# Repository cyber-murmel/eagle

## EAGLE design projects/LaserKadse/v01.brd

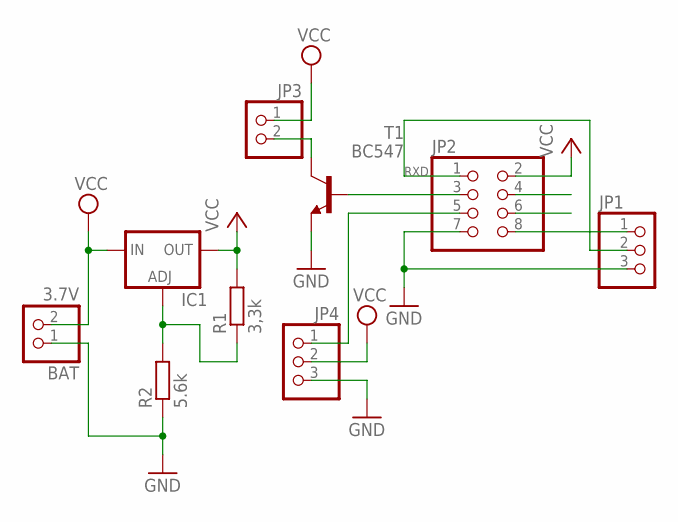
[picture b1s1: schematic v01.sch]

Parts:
BAT: 3.7V; 1X02/90
IC1: LM317TL; 317TL
JP1: PINHD-1X3/90; 1X03/90
JP2: PINHD-2X4; 2X04
JP3: PINHD-1X2; 1X02
JP4: PINHD-1X3; 1X03
R1: 3,3k; 0207/10
R2: 5.6k; 0207/10
T1: BC547; TO92

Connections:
BAT: BAT.2, IC1.3 (IN), JP3.1, JP4.2
CHPD: JP2.6
GND: BAT.1, JP1.3, JP2.7, JP4.3, R2.1, T1.1 (E)
GPIO0: JP2.3, T1.2 (B)
GPIO2: JP2.5, JP4.1
unnamed: IC1.1 (ADJ), R1.1, R2.2
unnamed: JP3.2, T1.3 (C)
unnamed: JP1.1, JP2.8
RST: JP2.4
RXD: JP1.2, JP2.1
VCC: IC1.2 (OUT), JP2.2, R1.2

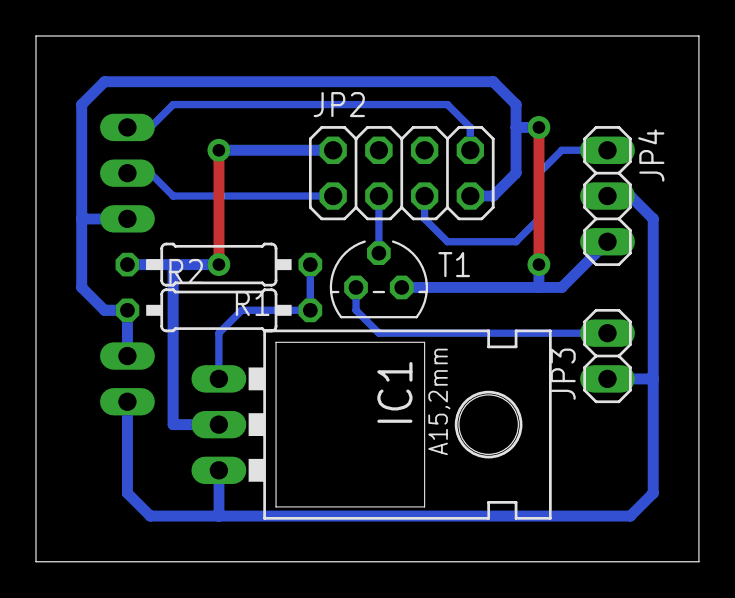
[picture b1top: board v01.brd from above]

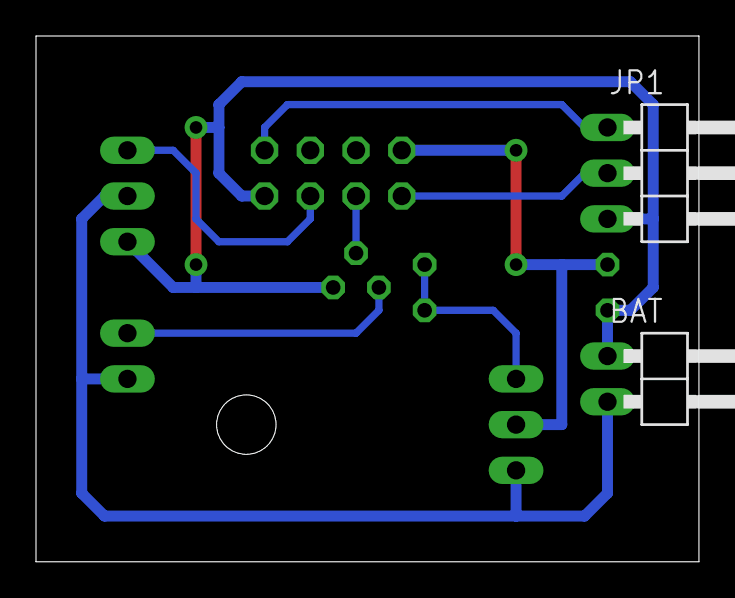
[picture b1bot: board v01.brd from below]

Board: 2 copper layers, 36.8 x 29.2 mm, 9 parts (2 on the bottom side), 9 nets.

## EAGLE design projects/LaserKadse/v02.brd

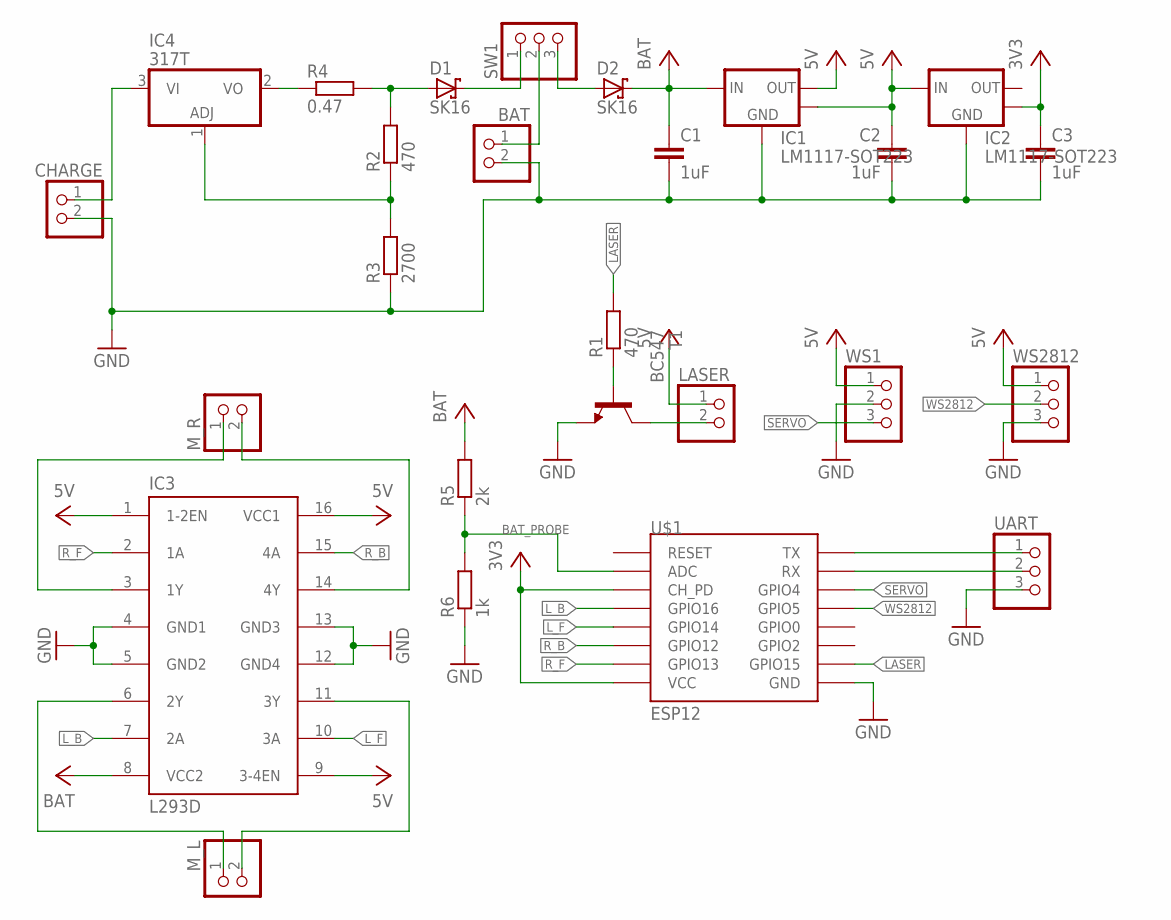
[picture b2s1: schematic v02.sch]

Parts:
BAT: PINHD-1X2; 1X02
C1, C2, C3: 1uF; C0805
CHARGE: PINHD-1X2; 1X02
D1, D2: SK16; SMB
IC1, IC2: LM1117-SOT223; SOT-223-3
IC3: L293D; DIL16
IC4: 317T; TO220H
LASER: PINHD-1X2; 1X02
M_L: PINHD-1X2; 1X02
M_R: PINHD-1X2; 1X02
R1, R2: 470; R0805
R3: 2700; R0805
R4: 0.47; MINI_MELF-0207W
R5: 2k; R0805
R6: 1k; R0805
SW1: PINHD-1X3; 1X03
T1: BC547; TO92
U$1: ESP12
UART: PINHD-1X3; 1X03
WS1, WS2812: PINHD-1X3; 1X03

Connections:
3V3: C3.1, IC2.4 (HEATSINK), U$1.CH_PD, U$1.VCC
5V: C2.1, IC1.4 (HEATSINK), IC2.3 (VIN), LASER.1, WS1.1, WS2812.1
5V_2: IC1.2 (VOUT), IC3.1 (1-2EN), IC3.9 (3-4EN), IC3.16 (VCC1)
BAT: C1.1, D2.C, IC1.3 (VIN), IC3.8 (VCC2), R5.2
BAT_PROBE: R5.1, R6.2, U$1.ADC
GND: BAT.2, C1.2, C2.2, C3.2, CHARGE.2, IC1.1 (GND), IC2.1 (GND), IC3.4 (GND1), IC3.5 (GND2), IC3.12 (GND4), IC3.13 (GND3), R3.1, R6.1, T1.1 (E), U$1.GND, UART.3, WS1.2, WS2812.3
LASER: R1.2, U$1.GPIO15
L_B: IC3.7 (2A), U$1.GPIO16
L_F: IC3.10 (3A), U$1.GPIO14
unnamed: BAT.1, SW1.2
unnamed: R1.1, T1.2 (B)
unnamed: CHARGE.1, IC4.3 (VI)
unnamed: D1.C, SW1.1
unnamed: IC3.3 (1Y), M_R.1
unnamed: IC3.14 (4Y), M_R.2
unnamed: IC3.6 (2Y), M_L.1
unnamed: IC3.11 (3Y), M_L.2
unnamed: U$1.TX, UART.1
unnamed: U$1.RX, UART.2
unnamed: LASER.2, T1.3 (C)
unnamed: D1.A, R2.2, R4.2
unnamed: IC4.1 (ADJ), R2.1, R3.2
unnamed: IC4.2 (VO), R4.1
unnamed: D2.A, SW1.3
R_B: IC3.15 (4A), U$1.GPIO12
R_F: IC3.2 (1A), U$1.GPIO13
SERVO: U$1.GPIO4, WS1.3
WS2812: U$1.GPIO5, WS2812.2

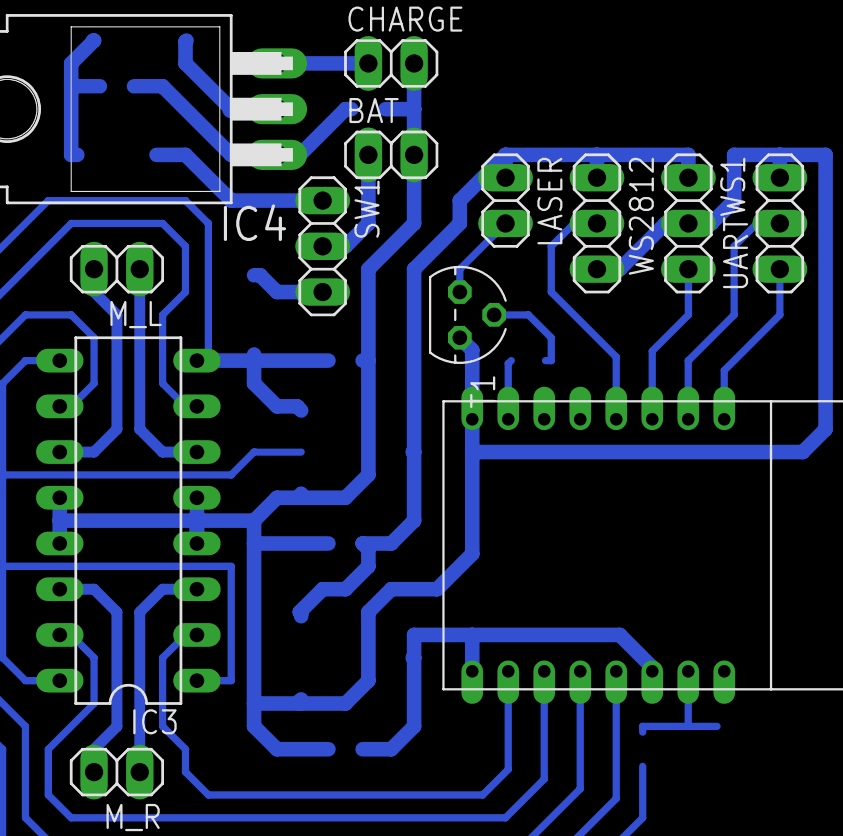
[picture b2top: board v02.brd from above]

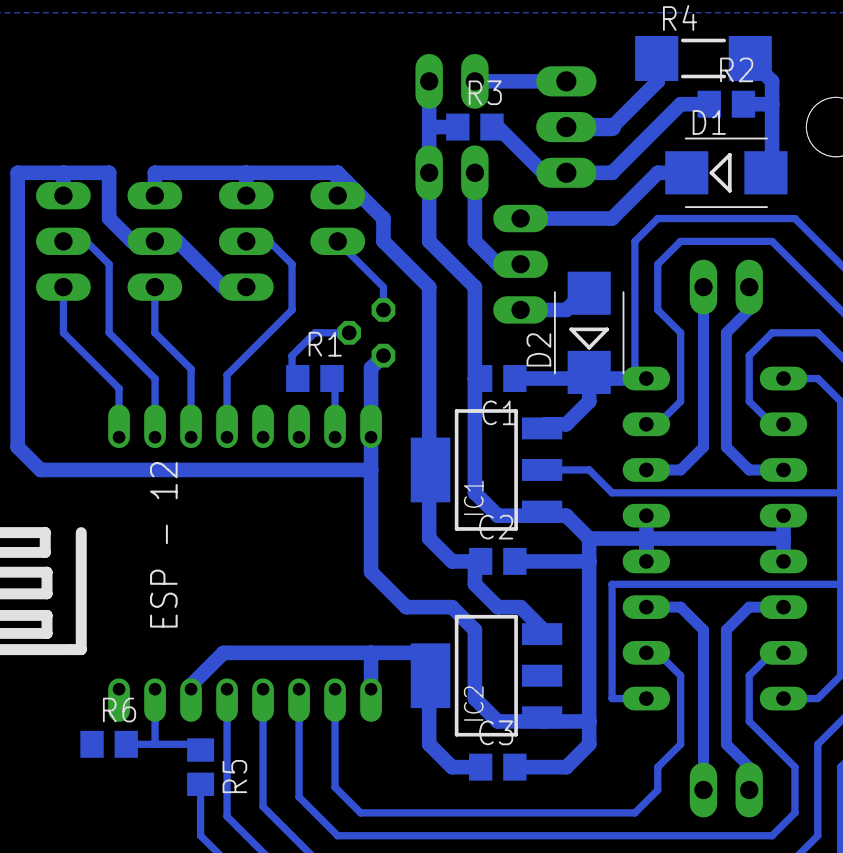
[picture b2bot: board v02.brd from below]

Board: 2 copper layers, 26 parts (14 on the bottom side), 28 nets.

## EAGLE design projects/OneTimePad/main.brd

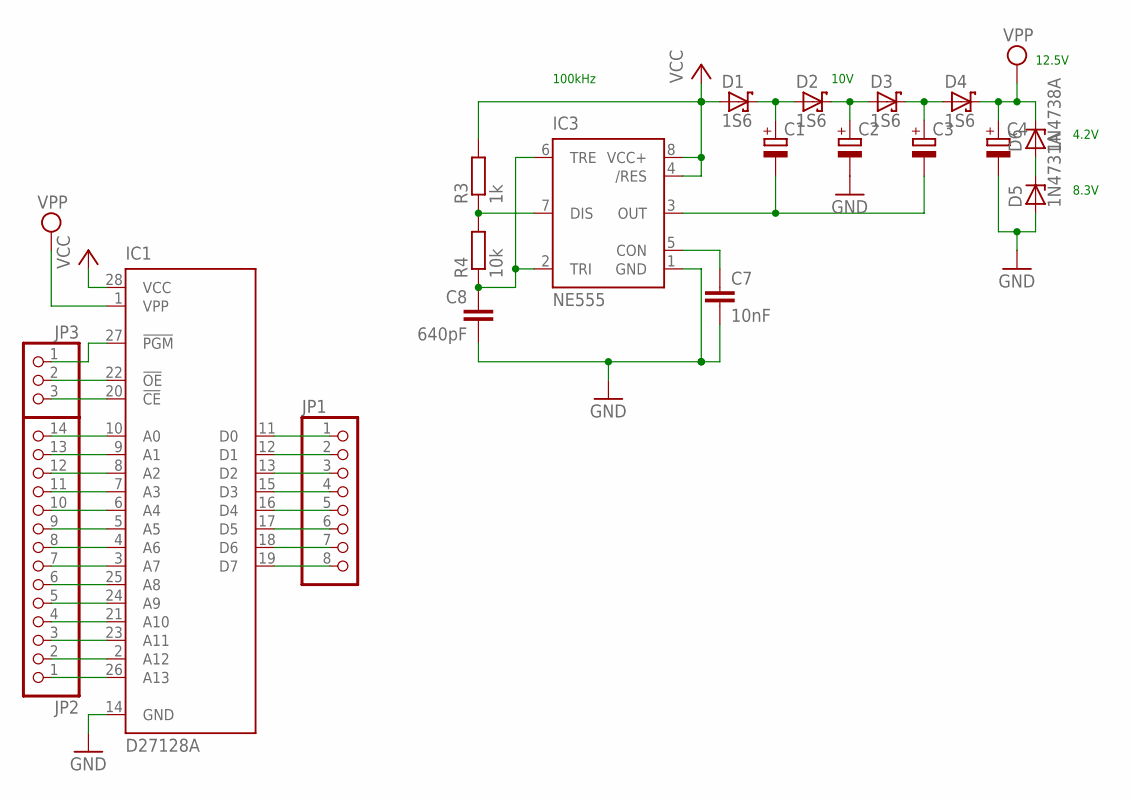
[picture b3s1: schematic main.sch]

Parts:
C1, C2, C3, C4: CPOL-EUB45181A; B45181A
C7: 10nF; C025-025X050
C8: 640pF; C025-025X050
D1, D2, D3, D4: 1S6; DO41-7.6
D5: 1N4731A; DO41Z10
D6: 1N4738A; DO41Z10
IC1: D27128A; DIL28-6
IC3: NE555; DIL-08
JP1: PINHD-1X8; 1X08
JP2: PINHD-1X14; 1X14
JP3: PINHD-1X3; 1X03
R3: 1k; 0204/7
R4: 10k; 0204/7

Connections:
GND: C2.-, C4.-, C7.2, C8.2, D5.A, IC1.14 (GND), IC3.1 (GND)
unnamed: IC1.11 (D0), JP1.1
unnamed: IC1.12 (D1), JP1.2
unnamed: IC1.13 (D2), JP1.3
unnamed: IC1.15 (D3), JP1.4
unnamed: IC1.16 (D4), JP1.5
unnamed: IC1.17 (D5), JP1.6
unnamed: IC1.18 (D6), JP1.7
unnamed: IC1.19 (D7), JP1.8
unnamed: IC1.10 (A0), JP2.14
unnamed: IC1.9 (A1), JP2.13
unnamed: IC1.8 (A2), JP2.12
unnamed: IC1.7 (A3), JP2.11
unnamed: IC1.6 (A4), JP2.10
unnamed: IC1.5 (A5), JP2.9
unnamed: IC1.4 (A6), JP2.8
unnamed: IC1.3 (A7), JP2.7
unnamed: IC1.25 (A8), JP2.6
unnamed: IC1.24 (A9), JP2.5
unnamed: IC1.21 (A10), JP2.4
unnamed: IC1.23 (A11), JP2.3
unnamed: IC1.2 (A12), JP2.2
unnamed: IC1.26 (A13), JP2.1
unnamed: C1.-, C3.-, IC3.3 (OUT)
unnamed: C3.+, D3.C, D4.A
unnamed: IC1.20 (!CE), JP3.3
unnamed: D5.C, D6.A
unnamed: IC1.22 (!OE), JP3.2
unnamed: IC1.27 (!PGM), JP3.1
unnamed: C7.1, IC3.5 (CON)
unnamed: C8.1, IC3.2 (TRI), IC3.6 (TRE), R4.1
unnamed: C1.+, D1.C, D2.A
unnamed: C2.+, D2.C, D3.A
unnamed: IC3.7 (DIS), R3.1, R4.2
VCC: D1.A, IC1.28 (VCC), IC3.4 (/RES), IC3.8 (VCC+), R3.2
VPP: C4.+, D4.C, D6.C, IC1.1 (VPP)

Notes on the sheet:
100kHz
10V
8.3V
4.2V
12.5V

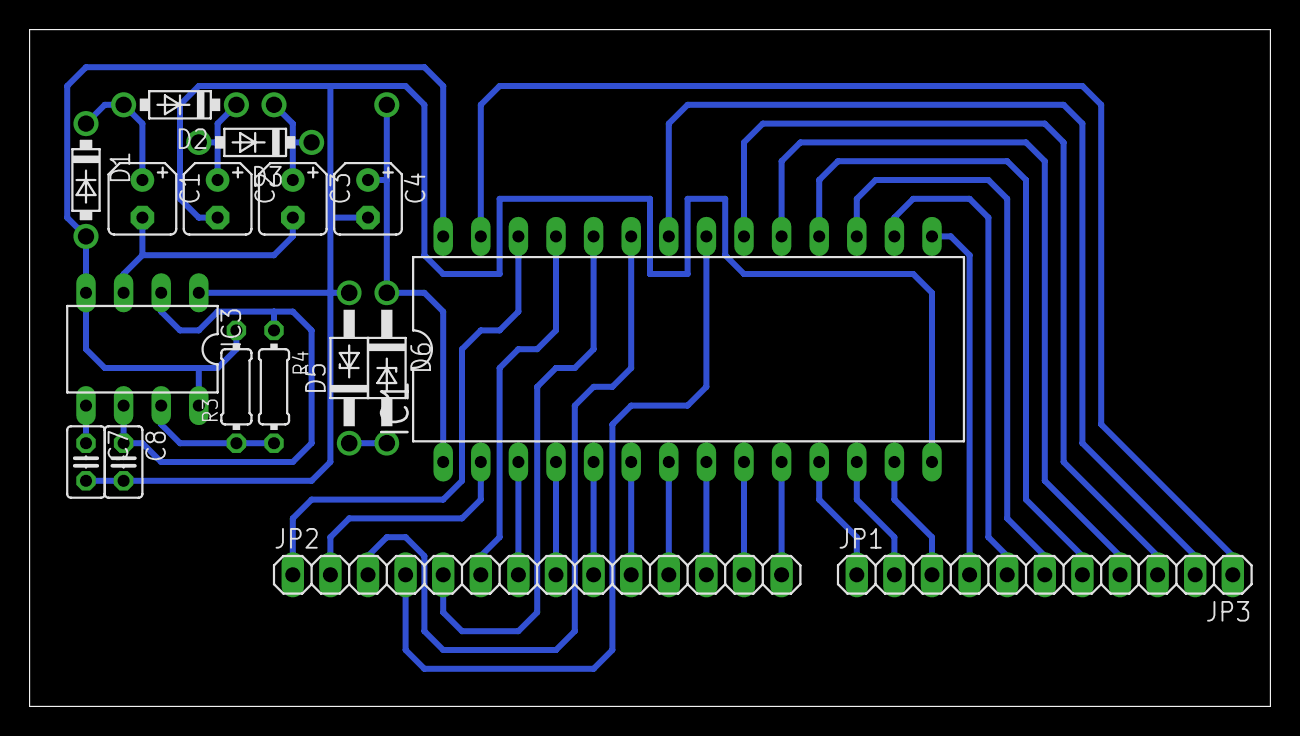
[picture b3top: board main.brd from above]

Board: 2 copper layers, 83.8 x 45.7 mm, 19 parts (1 on the bottom side), 36 nets.

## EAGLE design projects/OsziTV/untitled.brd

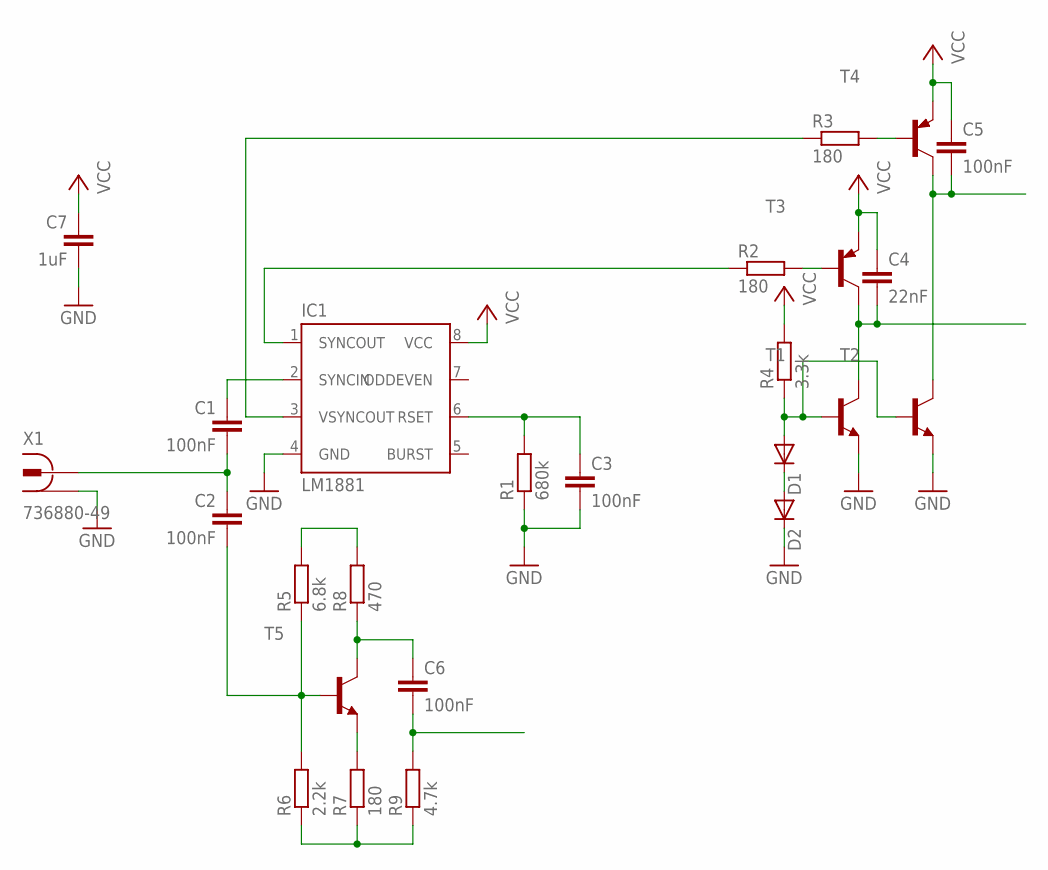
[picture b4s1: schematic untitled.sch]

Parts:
C1, C2, C3, C5, C6: 100nF; C0805
C4: 22nF; C0805
C7: 1uF; C0805
D1, D2: DIODE-MELF-MLL41; MELF-MLL41
IC1: LM1881; DIL08
R1: 680k; R0805
R2, R3, R7: 180; R0805
R4: 3.3k; R0805
R5: 6.8k; R0805
R6: 2.2k; R0805
R8: 470; R0805
R9: 4.7k; R0805
T1, T2, T5: -NPN-SOT23-EBC; SOT23-EBC
T3, T4: -PNP-SOT23-BCE; SOT23-BCE
X1: 736880-49

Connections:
GND: C3.2, C7.2, D2.C, IC1.4 (GND), R1.1, T1.E, T2.E, X1.1, X1.1@1 (1), X1.1@2 (1)
unnamed: IC1.3 (VSYNCOUT), R3.1
unnamed: C1.1, IC1.2 (SYNCIN)
unnamed: IC1.1 (SYNCOUT), R2.1
unnamed: C3.1, IC1.6 (RSET), R1.2
unnamed: R3.2, T4.B
unnamed: C1.2, C2.1, X1.2
unnamed: R2.2, T3.B
unnamed: C2.2, R5.1, R6.2, T5.B
unnamed: C5.2, T2.C, T4.C
unnamed: C4.2, T1.C, T3.C
unnamed: D1.C, D2.A
unnamed: D1.A, R4.1, T1.B, T2.B
unnamed: R5.2, R8.2
unnamed: R6.1, R7.1, R9.1
unnamed: R7.2, T5.E
unnamed: C6.1, R8.1, T5.C
unnamed: C6.2, R9.2
VCC: C4.1, C5.1, C7.1, IC1.8 (VCC), R4.2, T3.E, T4.E

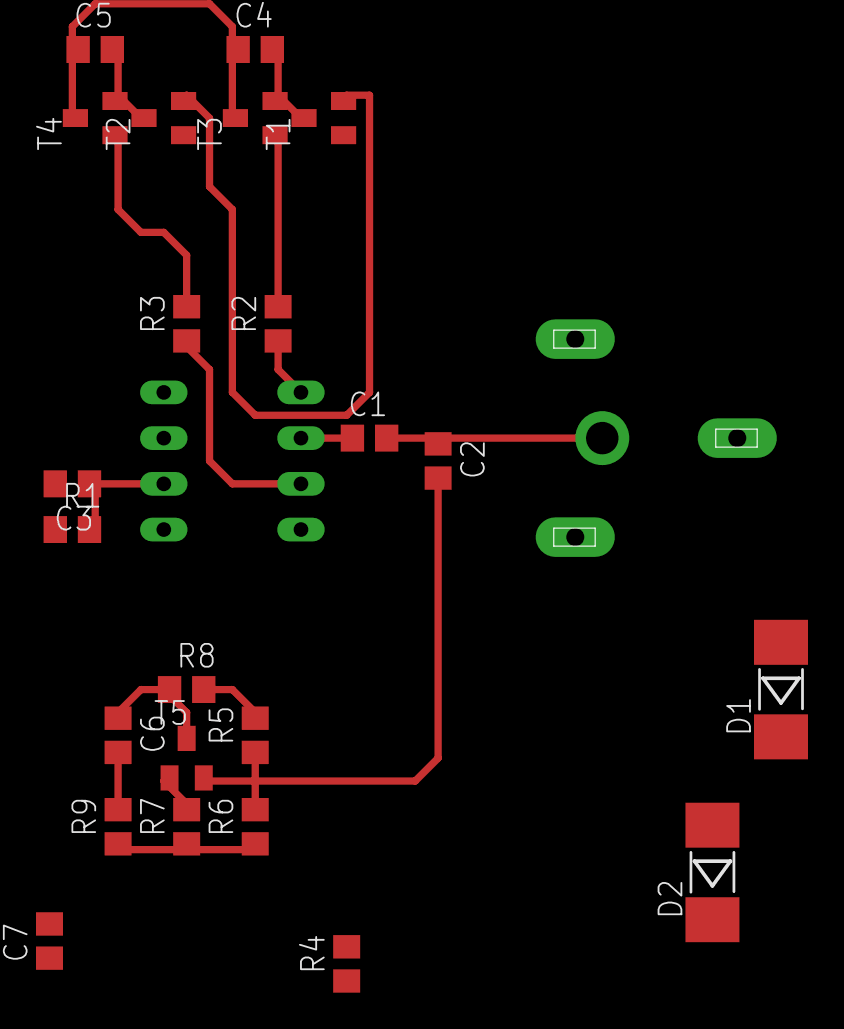
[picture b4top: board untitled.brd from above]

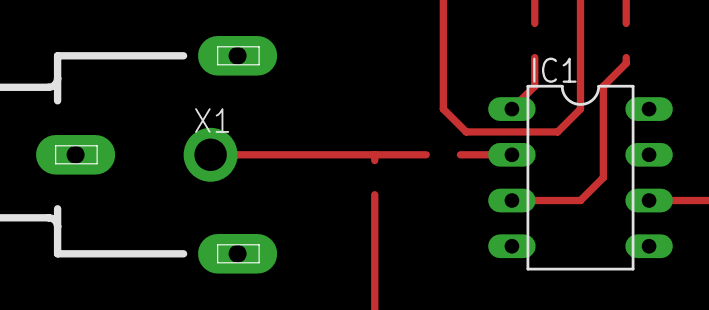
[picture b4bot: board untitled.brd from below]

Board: 2 copper layers, 25 parts (2 on the bottom side), 19 nets.

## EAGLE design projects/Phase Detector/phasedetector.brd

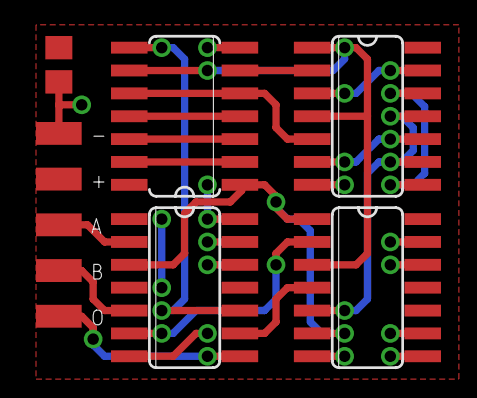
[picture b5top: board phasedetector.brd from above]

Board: 2 copper layers, 10 parts (0 on the bottom side), 19 nets.

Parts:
+: SMD1,27-2,54
-: SMD1,27-2,54
A: SMD1,27-2,54
B: SMD1,27-2,54
C1: 1uF; C0805
IC1: 74266; SO14
IC2: 7400; SO14
IC3: 7404; SO14
IC4: 74126; SO14
O: SMD1,27-2,54

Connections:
GND: -.1, C1.2, IC1.7, IC1.8, IC1.9, IC1.12, IC1.13, IC2.7, IC3.7, IC4.7, IC4.12, IC4.13
unnamed: IC1.5, IC2.9, IC2.11
unnamed: IC2.8, IC2.12
unnamed: IC1.3, IC2.1, IC2.4, IC3.9
unnamed: IC2.6, IC2.10
unnamed: IC2.3, IC2.13
unnamed: IC3.2, IC3.13
unnamed: IC3.3, IC3.12
unnamed: IC3.4, IC3.11
unnamed: IC2.5, IC3.5, IC3.10
unnamed: IC2.2, IC3.6
unnamed: IC1.4, IC4.9
unnamed: IC1.1, IC1.6, IC3.1, IC4.3
unnamed: A.1, IC4.2
unnamed: IC3.8, IC4.10
unnamed: IC4.8, O.1
unnamed: B.1, IC4.5
unnamed: IC1.2, IC4.6
VCC: +.1, C1.1, IC1.14, IC2.14, IC3.14, IC4.1, IC4.4, IC4.14

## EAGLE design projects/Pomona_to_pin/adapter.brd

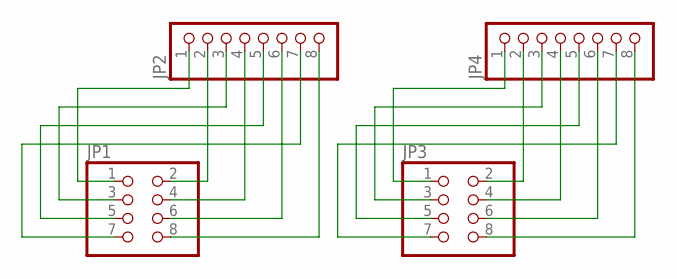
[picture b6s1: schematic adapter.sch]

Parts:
JP1, JP3: PINHD-2X4; 2X04
JP2, JP4: PINHD-1X8SMD_SMALL; 1X08/SMD_SMALL

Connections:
unnamed: JP1.1, JP2.1
unnamed: JP1.2, JP2.2
unnamed: JP1.3, JP2.3
unnamed: JP1.4, JP2.4
unnamed: JP1.5, JP2.5
unnamed: JP1.6, JP2.6
unnamed: JP1.7, JP2.7
unnamed: JP1.8, JP2.8
unnamed: JP3.1, JP4.1
unnamed: JP3.2, JP4.2
unnamed: JP3.3, JP4.3
unnamed: JP3.4, JP4.4
unnamed: JP3.5, JP4.5
unnamed: JP3.6, JP4.6
unnamed: JP3.7, JP4.7
unnamed: JP3.8, JP4.8

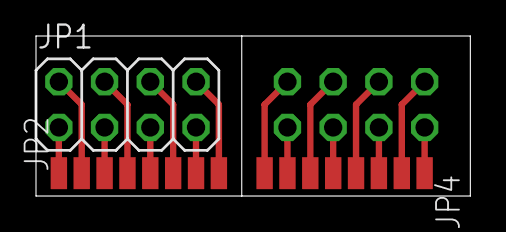
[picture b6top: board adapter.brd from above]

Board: 2 copper layers, 24.1 x 8.9 mm, 4 parts (1 on the bottom side), 16 nets.
